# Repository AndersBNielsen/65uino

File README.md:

# Welcome to the 65uino project

## Browser emulator

The self-contained [browser emulator](emulator/README.md) runs the real 65uino ROM. [Try it online](https://www.imania.dk/65uino-emulator/). From `emulator/`, run `npm test` and `npm run build`. Emulator code and bundled hardware/firmware assets have separate licenses; see [emulator/LICENSE.md](emulator/LICENSE.md).

It's a green 6502 based learning platform in a familiar form factor and a contestant in the 2023 Hackaday Prize. By taking IC's out of the waste stream and into useful products we encourage recycling and reuse.
It's a fun way to learn assembly programming and a tool you can use in your workshop for a lot more than you expect.

You can either make your own, get a PCB using the guide below or order a kit with SMD components presoldered from iMania.dk (IC's available if needed).

https://www.imania.dk/index.php?cPath=204&sort=5a&language=en

In this repository you will find KiCAD hardware files, gerbers and 6502 ASM source files for the 65uino.
The 65uino is based on the Single Breadboard Computer - https://youtu.be/s3t2QMukBRs

You'll find more details at https://hackaday.io/project/190260-65uino

Prerequisites:

Install cc65 (and minipro if using a tl866II+ to program a ROM - or, even better, check out the [Relatively Universal ROM Programmer](https://github.com/AndersBNielsen/Relatively-Universal-ROM-Programmer)!) using your favorite package manager
Run assemble.sh to assemble the source file
(If you use Windows you probably want to use WSL for this^)

The hardware schematic was created using KiCAD 6 & KiCAD 8

Be sure to check the complete getting started guide in the [docs folder](docs/getting-started/README.md)

## Getting a PCB
This project is kindly sponsored by JLCPCB. They offer cheap, professional looking PCBs and super fast delivery.

Step 1: Get the gerber file zip package from the /hardware folder

Step 2: Upload to JLCPCB [https://jlcpcb.com/?from=Anders_N](https://jlcpcb.com/?from=Anders_N)

Step 3: Pick your color, surface finish and order.

You can use these affiliate links to get a board for $2 and also get $54 worth of New User Coupons at: https://jlcpcb.com/?from=Anders_N

And in case you also want to order a 3D-printed case you can use this link. 
How to Get a $7 3D Printing Coupon: [https://3d.jlcpcb.com/?from=Anders3DP](https://jlc3dp.com/?from=Anders_N)

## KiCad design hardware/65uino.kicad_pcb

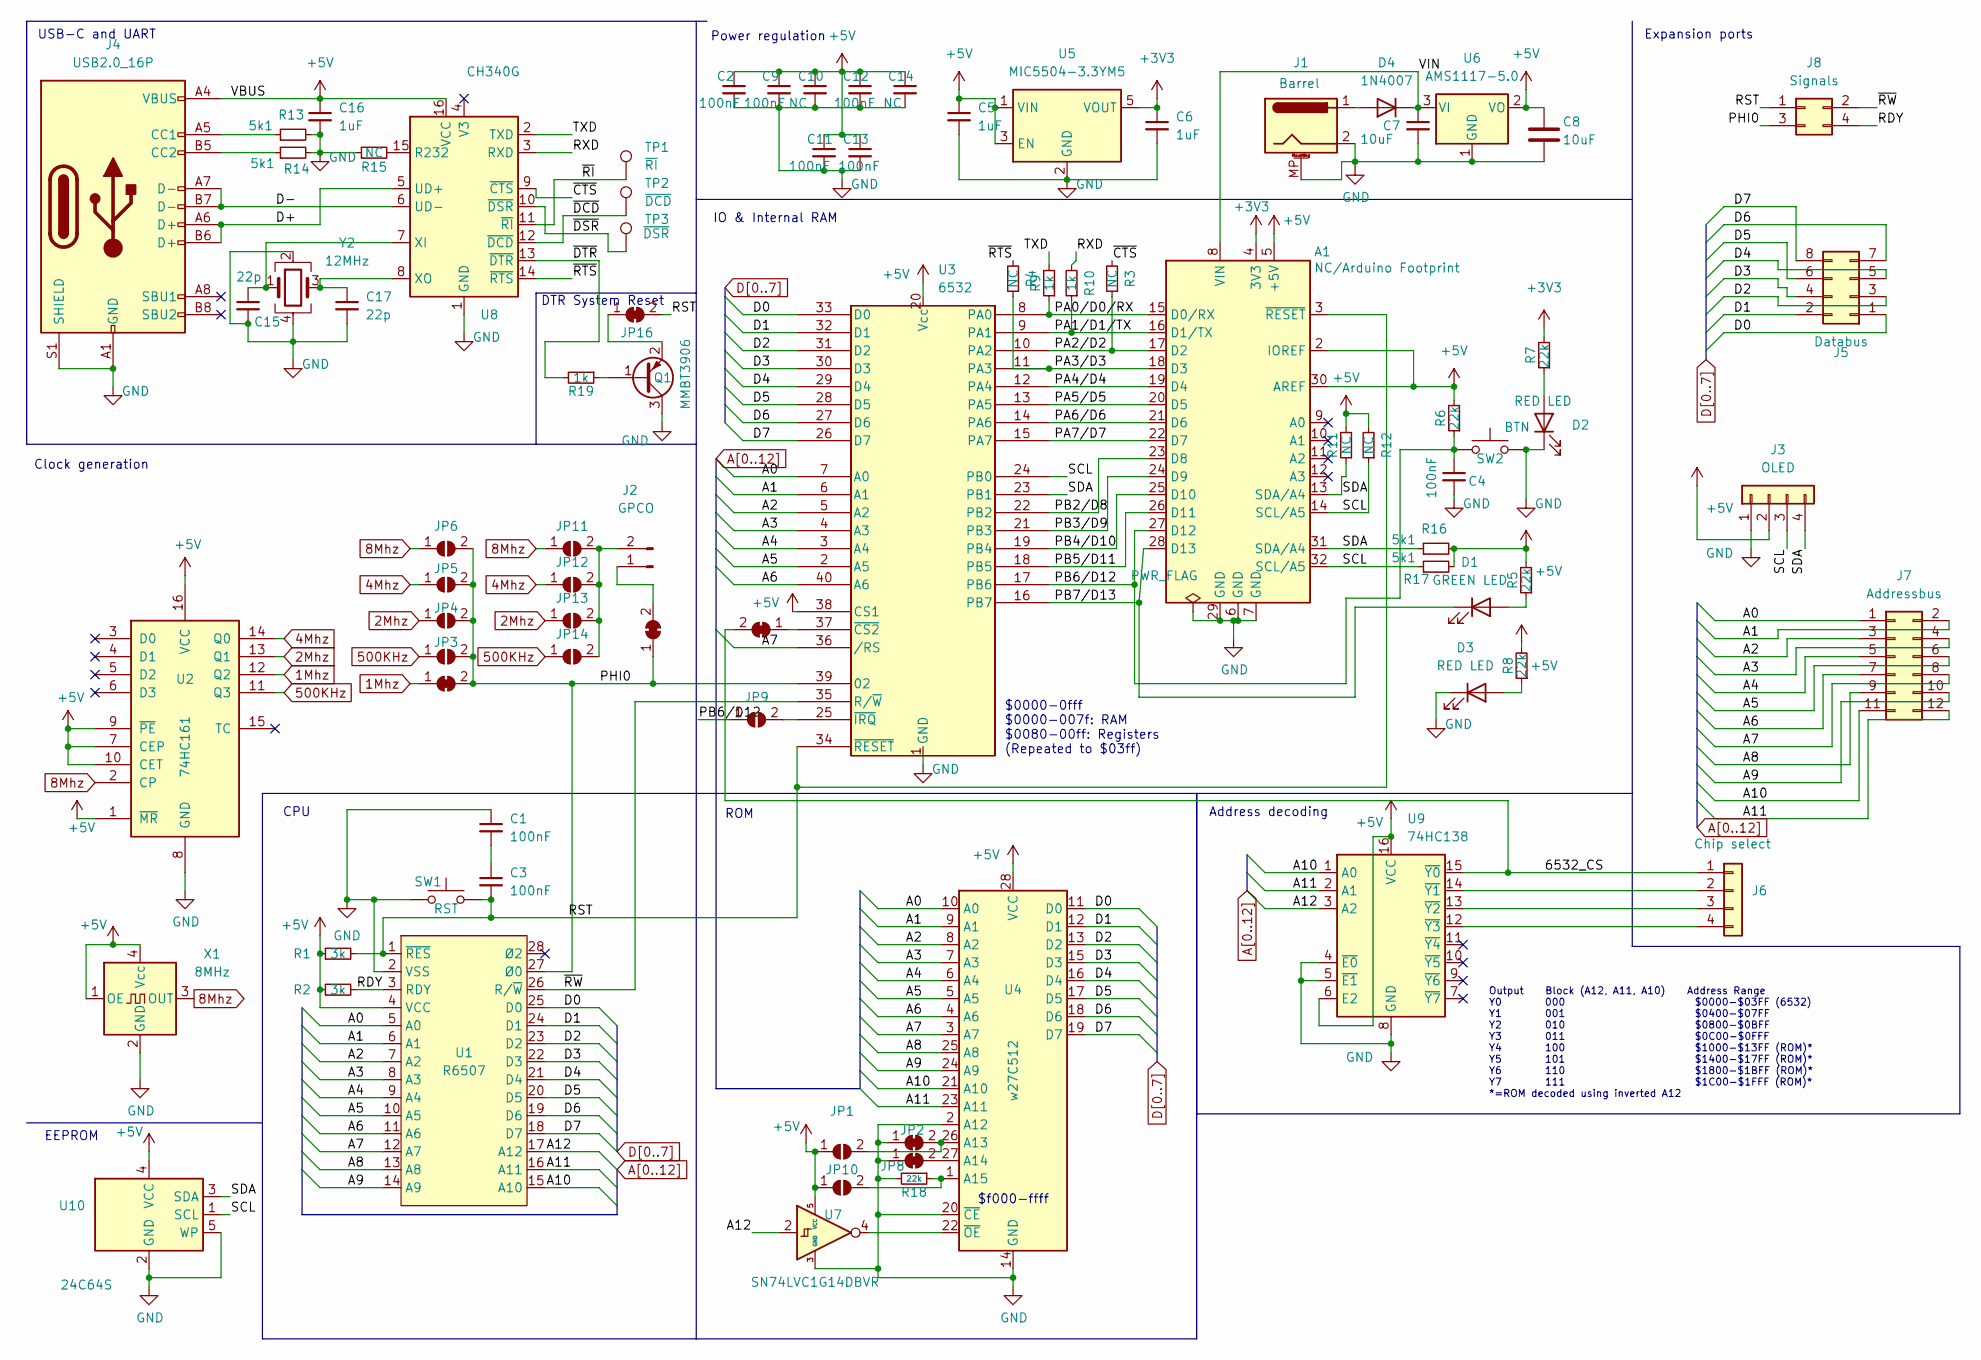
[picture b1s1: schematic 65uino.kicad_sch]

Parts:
A1: NC/Arduino Footprint; Arduino_UNO_R3_WithMountingHoles
C1, C2, C3, C4, C9, C11, C12, C13: 100nF; C_0805_2012Metric; LCSC C49678
C5, C6, C16: 1uF; C_0805_2012Metric; LCSC C28323
C7, C8: 10uF; C_1206_3216Metric; LCSC C13585
C10, C14: NC; C_0805_2012Metric
C15, C17: 22p; C_0805_2012Metric
D1: GREEN LED; LED_0805_2012Metric; LCSC C2297
D2, D3: RED LED; LED_0805_2012Metric; LCSC C84256
D4: 1N4007; D_SMA; LCSC C95872
J1: Barrel; BarrelJack_Horizontal
J2: GPCO; PinHeader_1x02_P2.54mm_Vertical
J3: OLED; PinSocket_1x04_P2.54mm_Vertical
J4: USB2.0_16P; USB_C_Receptacle_HCTL_HC-TYPE-C-16P-01A; LCSC C2894897
J5: Databus; PinHeader_2x04_P2.54mm_Vertical
J6: Chip select; PinSocket_1x04_P2.54mm_Vertical
J7: Addressbus; PinHeader_2x06_P2.54mm_Vertical
J8: Signals; PinHeader_2x02_P2.54mm_Vertical
JP1: SolderJumper_2_Open; SolderJumper-2_P1.3mm_Open_RoundedPad1.0x1.5mm
JP2, JP7, JP8, JP15, JP16, JP17: SolderJumper_2_Bridged; SolderJumper-2_P1.3mm_Bridged_RoundedPad1.0x1.5mm
JP3, JP4, JP5, JP6, JP9, JP11, JP12, JP13, JP14: SolderJumper_2_Bridged; SolderJumper-2_P1.3mm_Open_RoundedPad1.0x1.5mm
JP10: Jumper; PinHeader_1x02_P2.54mm_Vertical
Q1: MMBT3906; SOT-23; LCSC C7420354
R1, R2: 3k; R_0805_2012Metric; LCSC C17661
R3, R4, R11, R12, R15: NC; R_0805_2012Metric
R5, R6, R8, R18: 22k; R_0805_2012Metric; LCSC C17560
R7: 22k; R_0805_2012Metric; LCSC C17475
R9, R10, R19: 1k; R_0805_2012Metric
R13, R14, R16, R17: 5k1; R_0805_2012Metric
SW1: RST; SW_SPST_TL3342; LCSC C318884
SW2: BTN; SW_SPST_TL3342; LCSC C318884
TP1: ~{RI}; TestPoint_Pad_D1.0mm
TP2: ~{DCD}; TestPoint_Pad_D1.0mm
TP3: ~{DSR}; TestPoint_Pad_D1.0mm
U1: R6507; DIP-28_W15.24mm; LCSC C72121
U2: 74HC161; SOP-16_3.9x9.9mm_P1.27mm; LCSC C5310798
U3: 6532; DIP-40_W15.24mm; LCSC C72123
U4: w27C512; DIP-28_W15.24mm; LCSC C72121
U5: MIC5504-3.3YM5; SOT-23-5; LCSC C3021093
U6: AMS1117-5.0; SOT-223-3_TabPin2; LCSC C347223
U7: SN74LVC1G14DBVR; SOT-23-5; LCSC C434069
U8: CH340G; SOIC-16_3.9x9.9mm_P1.27mm; LCSC C14267
U9: 74HC138; SOP-16_3.9x9.9mm_P1.27mm; LCSC C2906780
U10: 24C64S; SOT-23-5; LCSC C7466824
X1: 8MHz; Crystal_SMD_3225-4Pin_3.2x2.5mm; LCSC C454610
Y2: 12MHz; Crystal_SMD_3225-4Pin_3.2x2.5mm; LCSC C133334

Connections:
1Mhz: JP7.1 (A), U2.12 (Q2)
2Mhz: JP4.1 (A), JP13.1 (A), U2.13 (Q1)
4Mhz: JP5.1 (A), JP12.1 (A), U2.14 (Q0)
8Mhz: JP6.1 (A), JP11.1 (A), U2.2 (CP), X1.3 (OUT)
500KHz: JP3.1 (A), JP14.1 (A), U2.11 (Q3)
+3V3: A1.4 (3V3), C6.1, R7.2, U5.5 (VOUT)
+5V: A1.2 (IOREF), A1.5 (+5V), A1.30 (AREF), C2.1, C5.1, C8.1, C9.1, C10.1, C11.1, C12.1, C13.1, C14.1, C16.1, J3.2, J4.A4 (VBUS), J4.A9 (VBUS), J4.B4 (VBUS), J4.B9 (VBUS), JP1.1 (A), JP10.1 (A), R1.1, R2.1, R5.2, R6.2, R8.2, R11.2, R12.2, R16.2, R17.2, U1.4 (VCC), U2.1 (~MR), U2.7 (CEP), U2.9 (~PE), U2.10 (CET), U2.16 (VCC), U3.20 (Vcc), U3.38 (CS1), U4.28 (VCC), U5.1 (VIN), U5.3 (EN), U6.2 (VO), U7.5 (VCC), U8.16 (VCC), U9.6 (E2), U9.16 (VCC), U10.4 (VCC), X1.1 (OE), X1.4 (Vcc)
/6532_CS: J6.1, JP17.2 (B), U9.15 (~Y0)
/D+: J4.A6 (D+), J4.B6 (D+), U8.5 (UD+)
/D-: J4.A7 (D-), J4.B7 (D-), U8.6 (UD-)
/PA0/D0/RX: A1.15 (D0/RX), R9.1, U3.8 (PA0)
/PA1/D1/TX: A1.16 (D1/TX), R10.1, U3.9 (PA1)
/PA2/D2: A1.17 (D2), R3.1, U3.10 (PA2)
/PA3/D3: A1.18 (D3), R4.1, U3.11 (PA3)
/PA4/D4: A1.19 (D4), U3.12 (PA4)
/PA5/D5: A1.20 (D5), U3.13 (PA5)
/PA6/D6: A1.21 (D6), U3.14 (PA6)
/PA7/D7: A1.22 (D7), U3.15 (PA7)
/PB2/D8: A1.23 (D8), U3.22 (PB2)
/PB3/D9: A1.24 (D9), U3.21 (PB3)
/PB4/D10: A1.25 (D10), U3.19 (PB4)
/PB5/D11: A1.26 (D11), U3.18 (PB5)
/PB6/D12: A1.27 (D12), C4.1, JP9.1 (A), R6.1, SW2.1, U3.17 (PB6)
/PB7/D13: A1.28 (D13), D1.1 (K), U3.16 (PB7)
/PHI0: J8.3, JP3.2 (B), JP4.2 (B), JP5.2 (B), JP6.2 (B), JP7.2 (B), JP15.1 (A), U1.27 (Ø0), U3.39 (02)
/RDY: J8.4, R2.2, U1.3 (RDY)
/RST: A1.3 (~RESET), C3.2, J8.1, JP16.2 (B), R1.2, SW1.2, U1.1 (~RES), U3.34 (~RESET)
/RXD: R10.2, U8.3 (RXD)
/SCL: A1.14 (SCL/A5), A1.32 (SCL/A5), J3.3, R12.1, R17.1, U3.24 (PB0), U10.1 (SCL)
/SDA: A1.13 (SDA/A4), A1.31 (SDA/A4), J3.4, R11.1, R16.1, U3.23 (PB1), U10.3 (SDA)
/TXD: R9.2, U8.2 (TXD)
/VIN: A1.8 (VIN), C7.1, D4.1 (K), U6.3 (VI)
/~CTS: R3.2, U8.9 (~CTS)
/~DCD: TP2.1, U8.12 (~DCD)
/~DSR: TP3.1, U8.10 (~DSR)
/~DTR: R19.2, U8.13 (~DTR)
/~RI: TP1.1, U8.11 (~RI)
/~RTS: R4.2, U8.14 (~RTS)
/~RW: J8.2, U1.26 (R/~W), U3.35 (R/~W)
A0: J7.1, U1.5 (A0), U3.7 (A0), U4.10 (A0)
A1: J7.2, U1.6 (A1), U3.6 (A1), U4.9 (A1)
A2: J7.3, U1.7 (A2), U3.5 (A2), U4.8 (A2)
A3: J7.4, U1.8 (A3), U3.4 (A3), U4.7 (A3)
A4: J7.5, U1.9 (A4), U3.3 (A4), U4.6 (A4)
A5: J7.6, U1.10 (A5), U3.2 (A5), U4.5 (A5)
A6: J7.7, U1.11 (A6), U3.40 (A6), U4.4 (A6)
A7: J7.8, U1.12 (A7), U3.36 (/RS), U4.3 (A7)
A8: J7.9, U1.13 (A8), U4.25 (A8)
A9: J7.10, U1.14 (A9), U4.24 (A9)
A10: J7.11, U1.15 (A10), U4.21 (A10), U9.1 (A0)
A11: J7.12, U1.16 (A11), U4.23 (A11), U9.2 (A1)
A12: U1.17 (A12), U7.2, U9.3 (A2)
D0: J5.1, U1.25 (D0), U3.33 (D0), U4.11 (D0)
D1: J5.2, U1.24 (D1), U3.32 (D1), U4.12 (D1)
D2: J5.3, U1.23 (D2), U3.31 (D2), U4.13 (D2)
D3: J5.4, U1.22 (D3), U3.30 (D3), U4.15 (D3)
D4: J5.5, U1.21 (D4), U3.29 (D4), U4.16 (D4)
D5: J5.6, U1.20 (D5), U3.28 (D5), U4.17 (D5)
D6: J5.7, U1.19 (D6), U3.27 (D6), U4.18 (D6)
D7: J5.8, U1.18 (D7), U3.26 (D7), U4.19 (D7)
GND: A1.6 (GND), A1.7 (GND), A1.29 (GND), C1.1, C2.2, C4.2, C5.2, C6.2, C7.2, C8.2, C9.2, C10.2, C11.2, C12.2, C13.2, C14.2, C15.2, C16.2, C17.2, D2.1 (K), D3.1 (K), J1.2, J1.MP (MountPin), J3.1, J4.A1 (GND), J4.A12 (GND), J4.B1 (GND), J4.B12 (GND), J4.S1 (SHIELD), JP2.1 (A), JP8.1 (A), Q1.3 (C), R13.2, R14.2, R15.1, R18.2, SW1.1, SW2.2, U1.2 (VSS), U2.8 (GND), U3.1 (GND), U4.2 (A12), U4.14 (GND), U4.20 (~CE), U5.2 (GND), U6.1 (GND), U7.3 (GND), U8.1 (GND), U9.4 (~E0), U9.5 (~E1), U9.8 (GND), U10.2 (GND), U10.5 (WP), X1.2 (GND), Y2.2, Y2.4
unnamed: C1.2, C3.1
unnamed: D1.2 (A), R5.1
unnamed: D2.2 (A), R7.1
unnamed: D3.2 (A), R8.1
unnamed: D4.2 (A), J1.1
unnamed: J2.1, JP15.2 (B)
unnamed: J2.2, JP11.2 (B), JP12.2 (B), JP13.2 (B), JP14.2 (B)
unnamed: J4.A5 (CC1), R13.1
unnamed: J4.B5 (CC2), R14.1
unnamed: J6.2, U9.14 (~Y1)
unnamed: J6.3, U9.13 (~Y2)
unnamed: J6.4, U9.12 (~Y3)
unnamed: JP1.2 (B), JP2.2 (B), U4.26 (A13)
unnamed: JP8.2 (B), U4.27 (A14)
unnamed: JP9.2 (B), U3.25 (~IRQ)
unnamed: JP10.2 (B), R18.1, U4.1 (A15)
unnamed: JP16.1 (A), Q1.2 (E)
unnamed: JP17.1 (A), U3.37 (~CS2)
unnamed: Q1.1 (B), R19.1
unnamed: U4.22 (~OE), U7.4
unnamed: R15.2, U8.15 (R232)
unnamed: C15.1, U8.7 (XI), Y2.1
unnamed: C17.1, U8.8 (XO), Y2.3

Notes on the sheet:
ROM
EEPROM
DTR System Reset
Clock generation
CPU
Expansion ports
IO & Internal RAM
$0000-0fff $0000-007f: RAM $0080-00ff: Registers (Repeated to $03ff)
$f000-ffff
Power regulation
Output Block (A12, A11, A10) Address Range Y0 000 $0000-$03FF (6532) Y1 001 $0400-$07FF Y2 010 $0800-$0BFF Y3 011 $0C00-$0FFF Y4 100 $1000-$13FF (ROM)* Y5 101 $1400-$17FF (ROM)* Y6 110 $1800-$1BFF (ROM)* Y7 111 $1C00-$1FFF (ROM)* *=ROM decoded using inverted A12
USB-C and UART
Address decoding

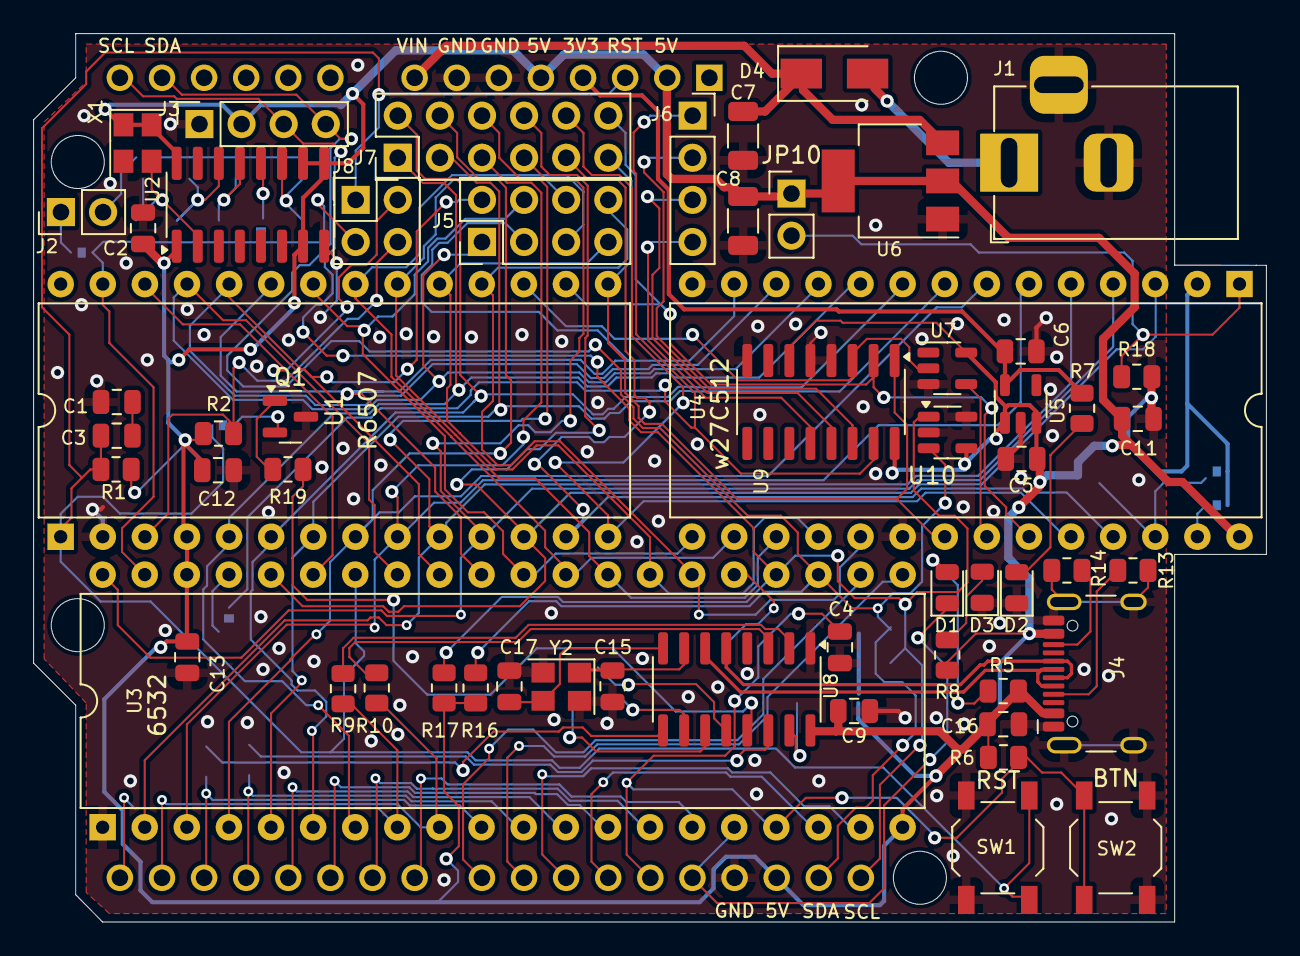
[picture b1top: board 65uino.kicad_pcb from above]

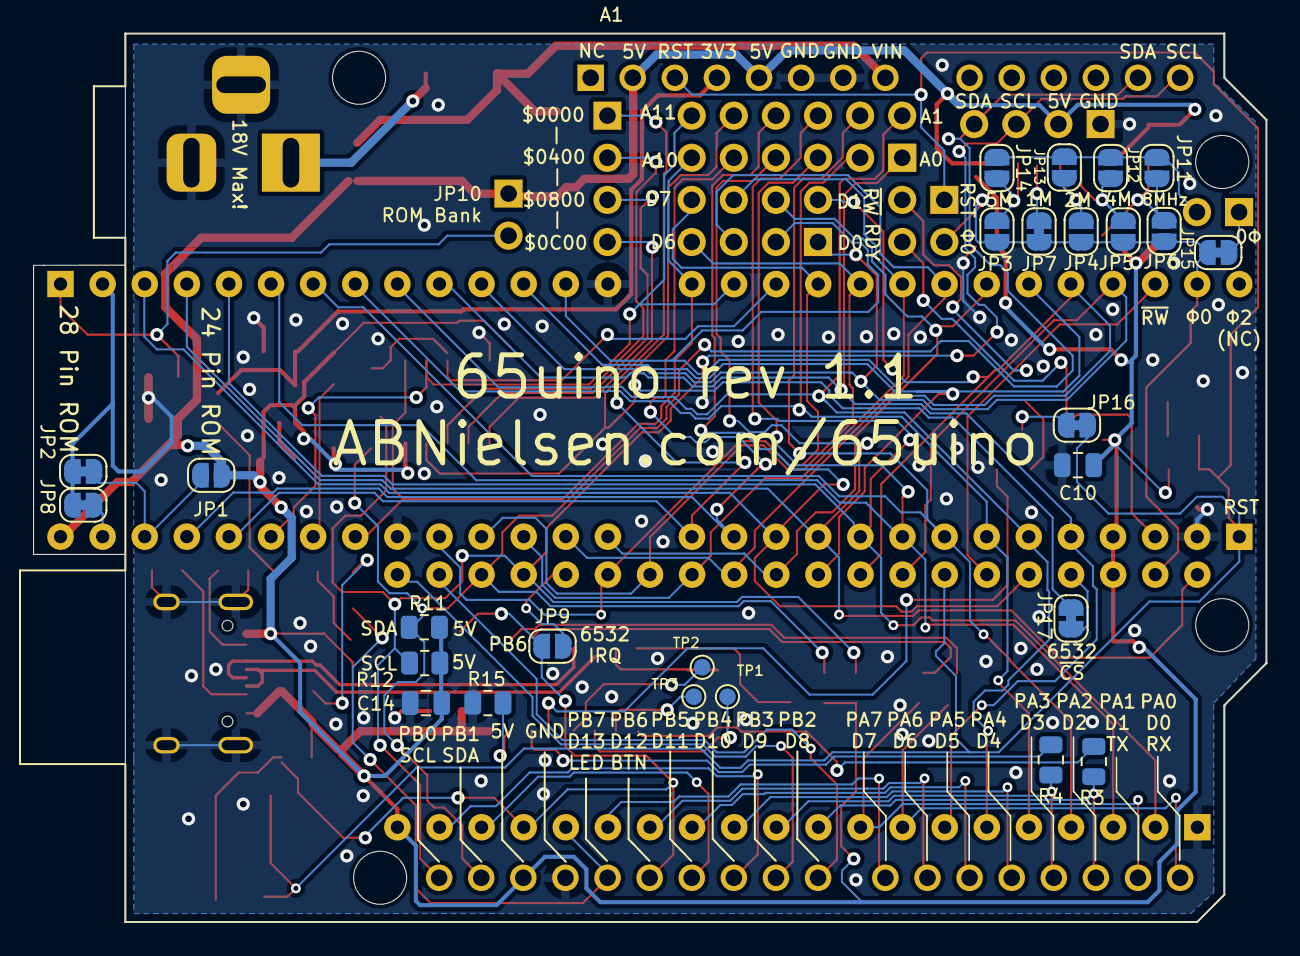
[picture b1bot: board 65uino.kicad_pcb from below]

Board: 2 copper layers, 74.4 x 53.6 mm, 84 parts (27 on the bottom side), 84 nets.

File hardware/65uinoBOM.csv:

"Reference","Value","Datasheet","Footprint","Qty","DNP","LCSC"
"A1","NC/Arduino Footprint","https://www.arduino.cc/en/Main/arduinoBoardUno","Module:Arduino_UNO_R3_WithMountingHoles","1","",""
"C3,C4,C9,C11,C12,C13","100nF","~","Capacitor_SMD:C_0805_2012Metric","6","","C49678"
"C5,C6,C16","1uF","~","Capacitor_SMD:C_0805_2012Metric","3","","C28323"
"C7,C8","10uF","~","Capacitor_SMD:C_1206_3216Metric","2","","C13585"
"C10,C14,R3,R4,R11,R12,R15","NC","~","-- mixed values --","7","",""
"C15,C17","22p","~","Capacitor_SMD:C_0805_2012Metric","2","",""
"D1","GREEN LED","~","LED_SMD:LED_0805_2012Metric","1","","C2297"
"D2,D3","RED LED","~","LED_SMD:LED_0805_2012Metric","2","","C84256"
"D4","1N4007","http://www.vishay.com/docs/88503/1n4001.pdf","Diode_SMD:D_SMA","1","","C95872"
"J1","Barrel","~","Connector_BarrelJack:BarrelJack_Horizontal","1","",""
"J2","GPCO","~","Connector_PinHeader_2.54mm:PinHeader_1x02_P2.54mm_Vertical","1","",""
"J3","OLED","~","Connector_PinSocket_2.54mm:PinSocket_1x04_P2.54mm_Vertical","1","",""
"J4","USB2.0_16P","https://www.usb.org/sites/default/files/documents/usb_type-c.zip","Connector_USB:USB_C_Receptacle_HCTL_HC-TYPE-C-16P-01A","1","","C2894897"
"J5","Databus","~","Connector_PinHeader_2.54mm:PinHeader_2x04_P2.54mm_Vertical","1","",""
"J6","Chip select","~","Connector_PinSocket_2.54mm:PinSocket_1x04_P2.54mm_Vertical","1","",""
"J7","Addressbus","~","Connector_PinHeader_2.54mm:PinHeader_2x06_P2.54mm_Vertical","1","",""
"J8","Signals","~","Connector_PinHeader_2.54mm:PinHeader_2x02_P2.54mm_Vertical","1","",""
"JP1","SolderJumper_2_Open","~","Jumper:SolderJumper-2_P1.3mm_Open_RoundedPad1.0x1.5mm","1","",""
"JP2,JP3,JP4,JP5,JP6,JP7,JP8,JP9,JP10,JP11,JP12,JP13,JP14,JP15,JP16,JP17","SolderJumper_2_Bridged","~","-- mixed values --","16","",""
"R1,R2","3k","~","Resistor_SMD:R_0805_2012Metric","2","","C17661"
"R5,R6,R7,R8","22k","~","Resistor_SMD:R_0805_2012Metric","4","","-- mixed values --"
"R9,R10,R16,R17","1k","~","Resistor_SMD:R_0805_2012Metric","4","",""
"R13,R14","5k1","~","Resistor_SMD:R_0805_2012Metric","2","",""
"SW1","RST","~","Button_Switch_SMD:SW_SPST_TL3342","1","","C318884"
"SW2","BTN","~","Button_Switch_SMD:SW_SPST_TL3342","1","","C318884"
"TP1","~{RI}","~","TestPoint:TestPoint_Pad_D1.0mm","1","",""
"TP2","~{DCD}","~","TestPoint:TestPoint_Pad_D1.0mm","1","",""
"TP3","~{DSR}","~","TestPoint:TestPoint_Pad_D1.0mm","1","",""
"U1","R6507","","Package_DIP:DIP-28_W15.24mm","1","","C72121"
"U2","74HC161","http://www.ti.com/lit/gpn/sn74LS161","Package_SO:SOP-16_3.9x9.9mm_P1.27mm","1","","C5310798"
"U3","6532","","Package_DIP:DIP-40_W15.24mm","1","","C72123"
"U4","w27C512","http://ww1.microchip.com/downloads/en/DeviceDoc/doc0015.pdf","Package_DIP:DIP-28_W15.24mm","1","","C72121"
"U5","MIC5504-3.3YM5","http://ww1.microchip.com/downloads/en/DeviceDoc/MIC550X.pdf","Package_TO_SOT_SMD:SOT-23-5","1","","C3021093"
"U6","AMS1117-5.0","http://www.ti.com/lit/ds/symlink/lm1117.pdf","Package_TO_SOT_SMD:SOT-223-3_TabPin2","1","","C347223"
"U7","SN74LVC1G14DBVR","http://www.ti.com/lit/ds/symlink/sn74lvc1g14.pdf","Package_TO_SOT_SMD:SOT-23-5","1","","C434069"
"U8","CH340G","http://www.datasheet5.com/pdf-local-2195953","Package_SO:SOIC-16_3.9x9.9mm_P1.27mm","1","","C14267"
"U9","74HC138","http://www.ti.com/lit/ds/symlink/cd74hc238.pdf","Package_SO:SOP-16_3.9x9.9mm_P1.27mm","1","","C2906780"
"X1","8MHz","https://support.epson.biz/td/api/doc_check.php?mode=dl&lang=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","Crystal:Crystal_SMD_3225-4Pin_3.2x2.5mm","1","","C454610"
"Y2","12MHz","~","Crystal:Crystal_SMD_3225-4Pin_3.2x2.5mm","1","","C133334"

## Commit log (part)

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2023-03-30 Gerbers and SMD osc. added
    First batch of PCB's ordered. Pads for an SMD oscillator added + extra decoupling pads.
2023-03-30 Gerbers updated
    Board house noted that a slot wasn't wide enough to mill. Space between USB tab and breakoff tab increased.
2023-04-22 SSD1306 routines + BMP180
    This update adds the basic routines needed to output text to an SSD1306 OLED display, including a font.
    Current state outputs a welcome text and updates the displayed raw BMP180 sensor temp data every loop tick.
2023-06-19 Update README.md
    Added note about WSL
2023-07-04 Net names, silkscreen, software serial
    Spoilers! :)
    This has some hardware improvements but the gerber files haven't been updated this time (plot them from KiCAD).
    There's also a spoiler for a future video: Software serial receives characters and outputs to screen.
2023-07-07 68.6mm
    Edge cuts
2023-08-06 Serial bootloader
    Upgraded to include serial bootloader code - code in sync with latest video.
2023-08-14 Pullups on serial and i2c lines + Single gate sot23-5 inverter default
    Added some "optional" pullups on the serial lines and i2c lines. Default is now to use a 1 gate sot23-5 inverter for address decoding instead of the DIP14 inverter, as well as the SMD oscillator inst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
2023-08-17 Update abn6507rom.s
    Fix comment
2023-09-25 Better SSD1306 lib, automatic bootloading and more
    Better SSD1306 lib - Now does CR/NL + backspace
    Automatic bootloading
    Speed optimizations
2023-09-26 Gerbers updated to match KiCAD
2023-09-26 U2 silkscreen moved
2023-09-26 Manufacturing improvements
    MicroUSB changed to Amphenol 10118194
    5V regulator capacitors changed to 1206 10uF
    LCSC Parts numbers added
2023-09-27 Minor PCB update
    Gerbers regenerated
2023-09-30 Minor
2023-10-20 Hardware scrolling support
2023-10-29 Software and hardware serial flow control + mouse bites removed
    Mouse bites removed due to manufacturer policies - like "this looks like two boards"-surcharge.
2023-11-17 Renamed bom.. To contain bom
2023-11-17 Images
2024-01-19 Initial Getting started doc
2024-01-19 started assemble.sh walkthough
2024-01-19 script execution and userland
2024-01-19 Easy baudrate changes
    Default baudrate back to 9600. Baudrate can be lowered by setting BAUDRATE - XON/XOFF disabled in code for now.
2024-01-19 memory map and writing your code
2024-01-19 TOC added
2024-01-19 doc TOC bug fix
2024-02-20 Code separation, send_userland.py
    Code for i2c, ssd1306 and macros are put in separate files and included in abn6507.s instead
    send_userland.py handles sending the binary userland file via serial - less complicated and better cross platform support.
2024-03-28 Update to support slow programming EPROMs
    Update to support slow programming EPROMs - userland code currently just checks attached breadboard ROM programmer for a blank ROM or if it's identical to internal ROM.
2024-04-04 Fix bug in "fast" ROM programming
    BNE changed to BEQ in cloneROM routine - works for W27C512 again.
    Current userland clones a W27C512 - has commented out snippets for common tasks.
2024-04-29 Code update to support uploading binary ROM file via serial
    send_command.py supports commands like erasing ROM and enabling VPE for calibration
    send_binary.py supports sending binary ROM via serial to be written by the programmer
    read_binary reads back what's on the ROM
    PCB needs a quick fix before being ready for Rev1 (do not use as is - wait for Rev1 coming really soon or use Rev0 gerbers instead)
2024-05-23 Update to ROM Programmer scripts
    Should be moved over to the programmer repo, but for now, here's an update.
2024-05-24 Move ROM programmer scripts to that repo.
    Scripts moved to https://github.com/AndersBNielsen/Relatively-Universal-ROM-Programmer
2024-05-24 Programmer files as submodule
    6502 code still needs to be made an optional include and moved to Programmer repo.
2024-06-08 Typo fix
2024-06-26 Quick fix for burning whole 64K of W27C512
    Changed it so setting "lastpage" to FF in send_binary actually rolls over instead. Downside is lastpage cant be $FE - must be fixed.
2024-08-21 Update README.md in Getting-started
2024-09-09 Flappy Larus bundle!
    The 65uino now comes with entertainment included! Meet "Flappy Larus" - hours of arcade game fun for just a few bytes of RAM.
2024-12-12 Revision 1 - UART & Clock Divider
    UART, Clock Divider, extra address decoding and bus headers added - a full-fledged 6502 computer with an Uno footprint!
2025-01-03 Incomplete
2025-01-03 Rev 1 Serial Fix
    This adds appropriate delay to wait for DTR reboot for Rev1 and sets initial TX state correctly
2025-01-03 Gitignore
2025-01-29 Main Menu, Code Monitor, Airplane Mode, Inverted text
    Major update
    The 65uino now boots into a main menu system allowing the user to choose between features assembled into ROM. Long press USR button to select, short press for next. ROM Programmer code is not assembl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
    This version also comes with a code monitor, making it possible to view and edit 6502 instructions in RAM.
    Short press for next byte, long press to edit/write byte.
    Airplane mode - 6502 instruction $F2, aka JAM stops the CPU as much as is possible from software.
    fastprint has been integrated into ssd1306_sendchar using tflags variable.
2025-02-05 Rev1 Gerber Fix
    Connect U2 pin 9 and 10 for stable oscillator performance without solder blob
2025-02-08 Revision 1 photos
2025-02-19 Cleanup, new schematic PDF
    Old files moved to hardware/R0
    New schematic PDF and BOM csv created.
2025-04-24 Rev 1.1
    Rev 1.1 - working i2c scanner, default baud rate 4800, SOT23 EEPROM added
2025-07-25 i2c improvements and immature Si5351 driver
2025-11-30 Initial SDR
2025-12-03 Not quite there yet...
2025-12-12 Q1.14 wip
2025-12-14 Madness
2025-12-14 Sample ADC data -5860hz
2025-12-16 Sorta kinda working 6502 Goertzel
2025-12-18 Works - still overflows and wraps sometimes
2025-12-23 Working Goertzel - room for optimization

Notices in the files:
hardware/65uino.kicad_pcb:
License: https://creativecommons.org/licenses/by-nc/4.0/legalcode
